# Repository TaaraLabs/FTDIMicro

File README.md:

FTDI Micro
==========

[WebSite](https://taaralabs.eu/fu1)

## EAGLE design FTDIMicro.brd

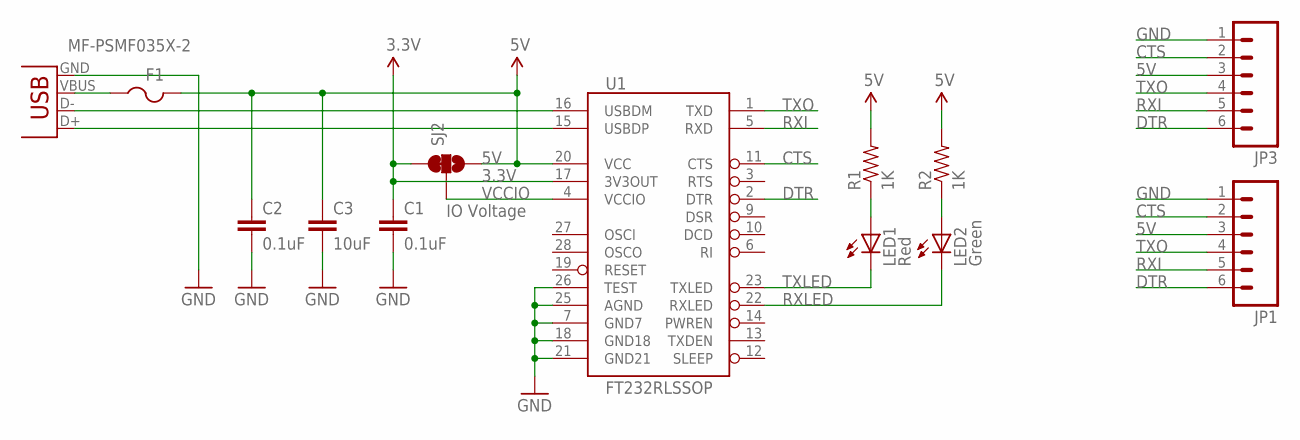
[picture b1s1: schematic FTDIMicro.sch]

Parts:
C1, C2: 0.1uF; 0603-CAP
C3: 10uF; 0603-CAP
F1: MF-PSMF035X-2; R1206
JP1, JP3: M06SMD-FEMALE-V2; 1X06-SMD-FEMALE-V2
LED1: Red; LED-0603
LED2: Green; LED-0603
R1, R2: 1K; 0603-RES
SJ2: SOLDERJUMPER_2WAYS; SJ_3
U1: FT232RLSSOP; SSOP28DB
X1: USB-MICROB

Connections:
3.3V: C1.1, SJ2.1, U1.17 (3V3OUT)
5V: C2.1, C3.1, F1.2, JP1.3, JP3.3, R1.2, R2.2, SJ2.3, U1.20 (VCC)
CTS: JP1.2, JP3.2, U1.11 (CTS)
DTR: JP1.6, JP3.6, U1.2 (DTR)
GND: C1.2, C2.2, C3.2, JP1.1, JP3.1, U1.7 (GND7), U1.18 (GND18), U1.21 (GND21), U1.25 (AGND), U1.26 (TEST), X1.GND
unnamed: LED1.A, R1.1
unnamed: LED2.A, R2.1
unnamed: F1.1, X1.VBUS
RXI: JP1.5, JP3.5, U1.5 (RXD)
RXLED: LED2.C, U1.22 (RXLED)
TXLED: LED1.C, U1.23 (TXLED)
TXO: JP1.4, JP3.4, U1.1 (TXD)
USB_D+: U1.15 (USBDP), X1.D+
USB_D-: U1.16 (USBDM), X1.D-
VCCIO: SJ2.2, U1.4 (VCCIO)

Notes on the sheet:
IO Voltage

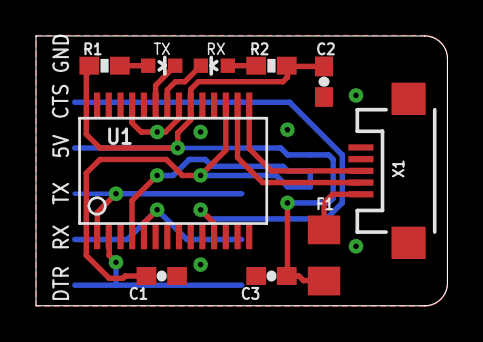
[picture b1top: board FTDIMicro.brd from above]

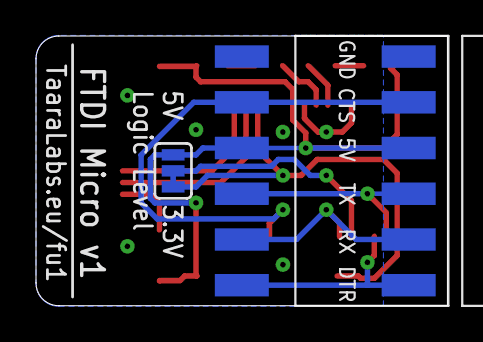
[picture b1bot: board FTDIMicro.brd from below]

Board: 2 copper layers, 22.9 x 15.0 mm, 13 parts (3 on the bottom side), 15 nets.

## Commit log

2015-02-01 :octocat: Added .gitattributes & .gitignore files
2015-02-01 FTDIMicro
